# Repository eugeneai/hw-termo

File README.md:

# hw-termo
Termometer student project ATMega16, hdc1080 ....

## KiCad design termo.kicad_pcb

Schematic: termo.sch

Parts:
C1, C3, C4: C; C_0805_2012Metric
C2, C5: CP; CP_Radial_D7.5mm_P2.50mm
C_block1: C; C_0805_2012Metric
J1: USB_A; USB_A_CNCTech_1001-011-01101_Horizontal
J2: Conn_01x04_Female; PinHeader_1x04_P2.54mm_Vertical
J3: ISP; PinHeader_2x03_P2.54mm_Vertical
J4: PA; PinHeader_1x08_P2.54mm_Vertical
J5: PB; PinHeader_1x08_P2.54mm_Vertical
J6: PC; PinHeader_1x08_P2.54mm_Vertical
J7: PD; PinHeader_1x08_P2.54mm_Vertical
J8: PWR; PinHeader_1x06_P2.54mm_Vertical
J9: PA; PinHeader_1x02_P2.54mm_Vertical
R1, R2, R3, R4, R5: R; R_0805_2012Metric
U1: AMS1117; SOT-223-3_TabPin2
U3: HDC1080; Texas_PWSON-N6
U_mega1: ATmega16-16AU; TQFP-44_10x10mm_P0.8mm
Y1: Crystal; Resonator-2Pin_W7.0mm_H2.5mm

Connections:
+3V3: C5.1, C_block1.1, J2.1, J8.3, J8.4, R3.1, R4.1, U1.2 (VO), U3.5 (VCC), U_mega1.5 (VCC), U_mega1.17 (VCC), U_mega1.38 (VCC)
+5V: C1.1, C2.1, J1.1 (VBUS), J3.2, J8.1, J8.2, U1.3 (VI)
GNDD: C1.2, C2.2, C3.1, C4.1, C5.2, C_block1.2, J1.4 (GND), J1.5 (Shield), J2.2, J3.6, J8.5, J8.6, U1.1 (ADJ), U3.2 (GND), U3.7 (GND), U_mega1.6 (GND), U_mega1.18 (GND), U_mega1.28 (GND), U_mega1.39 (GND)
unnamed: C3.2, R5.2, U_mega1.8 (XTAL1), Y1.1
unnamed: C4.2, R5.1, U_mega1.7 (XTAL2), Y1.2
unnamed: J1.2 (D-), R2.2
unnamed: J1.3 (D+), R1.2
unnamed: J4.1, U_mega1.37 (PA0)
unnamed: J4.2, U_mega1.36 (PA1)
unnamed: J4.3, U_mega1.35 (PA2)
unnamed: J4.4, U_mega1.34 (PA3)
unnamed: J4.5, U_mega1.33 (PA4)
unnamed: J4.6, U_mega1.32 (PA5)
unnamed: J4.7, U_mega1.31 (PA6)
unnamed: J4.8, U_mega1.30 (PA7)
unnamed: J5.1, U_mega1.40 (PB0)
unnamed: J5.2, U_mega1.41 (PB1)
unnamed: J5.3, U_mega1.42 (PB2)
unnamed: J5.4, U_mega1.43 (PB3)
unnamed: J5.5, U_mega1.44 (PB4)
unnamed: J6.3, U_mega1.21 (PC2)
unnamed: J6.4, U_mega1.22 (PC3)
unnamed: J6.5, U_mega1.23 (PC4)
unnamed: J6.6, U_mega1.24 (PC5)
unnamed: J6.7, U_mega1.25 (PC6)
unnamed: J6.8, U_mega1.26 (PC7)
unnamed: J7.1, U_mega1.9 (PD0)
unnamed: J7.2, U_mega1.10 (PD1)
unnamed: J7.5, U_mega1.13 (PD4)
unnamed: J7.6, U_mega1.14 (PD5)
unnamed: J7.7, U_mega1.15 (PD6)
unnamed: J7.8, U_mega1.16 (PD7)
aref: J9.2, U_mega1.29 (AREF)
avcc: J9.1, U_mega1.27 (AVCC)
d+: R1.1, U_mega1.11 (PD2)
d-: R2.1, U_mega1.12 (PD3)
miso: J3.1, J5.7, U_mega1.2 (PB6)
mosi: J3.4, J5.6, U_mega1.1 (PB5)
reset: J3.5, U_mega1.4 (~RESET)
sck: J3.3, J5.8, U_mega1.3 (PB7)
scl: J2.4, J6.1, R3.2, U3.6 (SCL), U_mega1.19 (PC0)
sda: J2.3, J6.2, R4.2, U3.1 (SDA), U_mega1.20 (PC1)

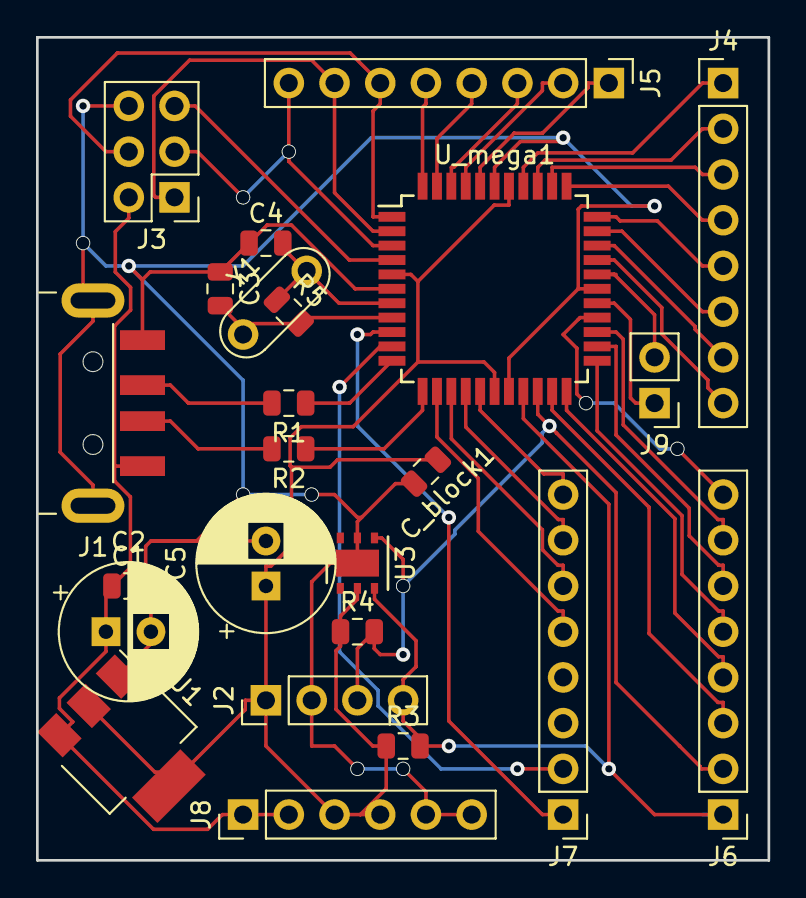
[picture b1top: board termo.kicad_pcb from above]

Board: 2 copper layers, 40.6 x 45.7 mm, 24 parts (0 on the bottom side), 42 nets.

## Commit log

2019-02-01 Initial import
2019-02-01 Final layout
2019-02-02 Added readme
